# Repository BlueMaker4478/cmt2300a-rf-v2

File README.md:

# cmt2300a-rf-v2
CMT2300A RF IC Solution Ultra-low Power Sub 433-868MHz RF Transceiver

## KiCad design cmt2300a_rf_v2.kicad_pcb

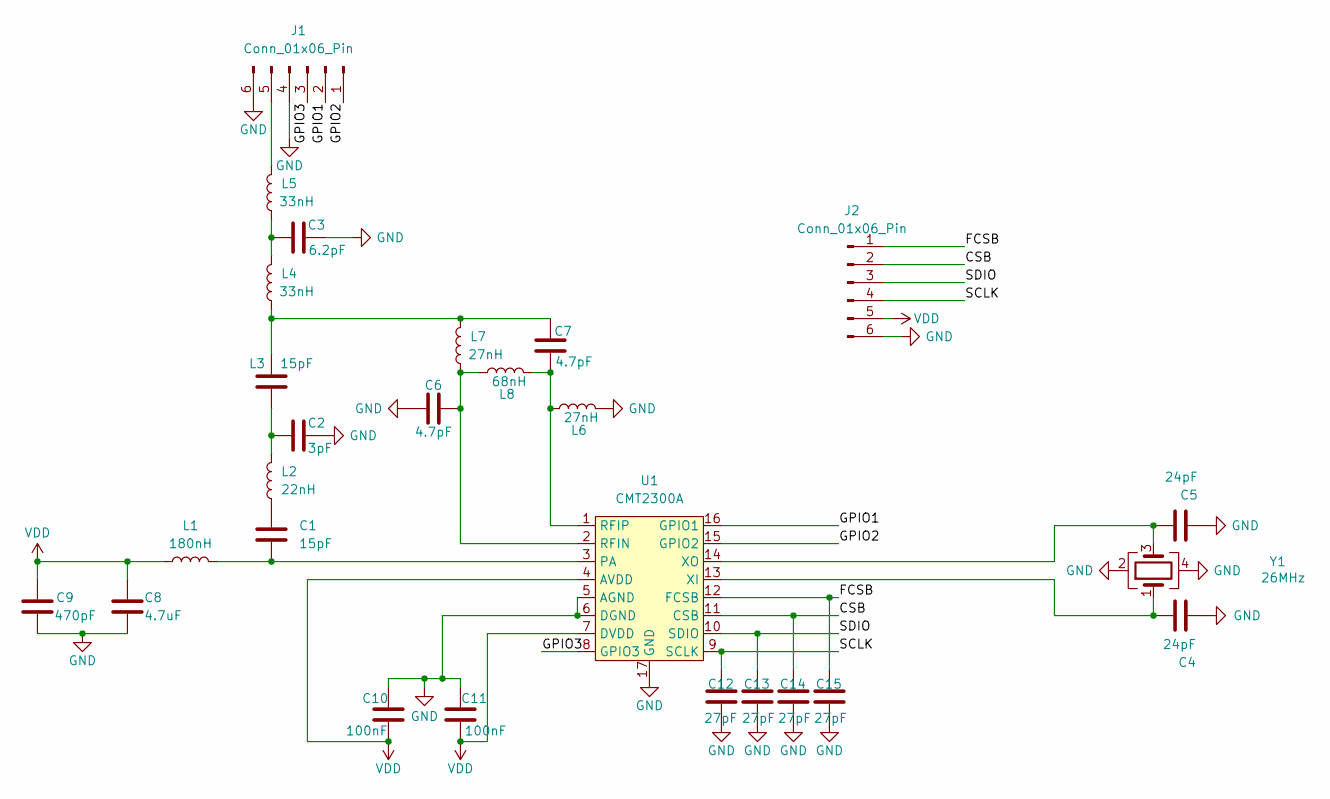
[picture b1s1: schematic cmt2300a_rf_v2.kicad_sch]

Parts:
C1: 15pF; C_0603_HandSolder
C2: 3pF; C_0603_HandSolder
C3: 6.2pF; C_0603_HandSolder
C4, C5: 24pF; C_0603_HandSolder
C6, C7: 4.7pF; C_0603_HandSolder
C8: 4.7uF; C_0603_HandSolder
C9: 470pF; C_0603_HandSolder
C10, C11: 100nF; C_0603_HandSolder
C12, C13, C14, C15: 27pF; C_0603_HandSolder
J1, J2: Conn_01x06_Pin; PinHeader_1x06_P2.54mm_Vertical
L1: 180nH; L_0603_HandSolder
L2: 22nH; L_0603_HandSolder
L3: 15pF; C_0603_HandSolder
L4, L5: 33nH; L_0603_HandSolder
L6, L7: 27nH; L_0603_HandSolder
L8: 68nH; L_0603_HandSolder
U1: CMT2300A; QFN-16-1EP_3x3mm_P0.5mm_EP1.7x1.7mm
Y1: 26MHz; Crystal_SMD_3225-4Pin_3.2x2.5mm

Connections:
/CSB: C14.1, J2.2, U1.11 (CSB)
/FCSB: C15.1, J2.1, U1.12 (FCSB)
/GPIO1: J1.2, U1.16 (GPIO1)
/GPIO2: J1.1, U1.15 (GPIO2)
/GPIO3: J1.3, U1.8 (GPIO3)
/SCLK: C12.1, J2.4, U1.9 (SCLK)
/SDIO: C13.1, J2.3, U1.10 (SDIO)
GND: C2.2, C3.2, C4.2, C5.2, C6.1, C8.2, C9.2, C10.1, C11.1, C12.2, C13.2, C14.2, C15.2, J1.4, J1.6, J2.6, L6.2, U1.5 (AGND), U1.6 (DGND), U1.17 (GND), Y1.2, Y1.4
unnamed: C1.1, L2.1
unnamed: C2.1, L2.2, L3.1
unnamed: C3.1, L4.2, L5.1
unnamed: C7.2, L3.2, L4.1, L7.2
unnamed: J1.5, L5.2
unnamed: C1.2, L1.2, U1.3 (PA)
unnamed: C6.2, L7.1, L8.1, U1.2 (RFIN)
unnamed: C7.1, L6.1, L8.2, U1.1 (RFIP)
unnamed: C4.1, U1.13 (XI), Y1.1
unnamed: C5.1, U1.14 (XO), Y1.3
VDD: C8.1, C9.1, C10.2, C11.2, J2.5, L1.1, U1.4 (AVDD), U1.7 (DVDD)

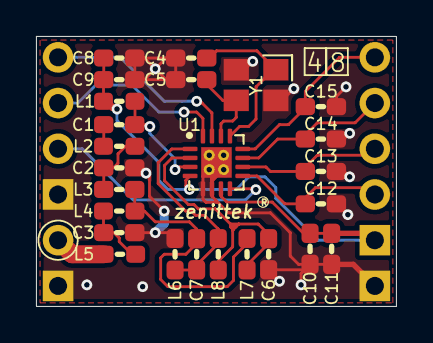
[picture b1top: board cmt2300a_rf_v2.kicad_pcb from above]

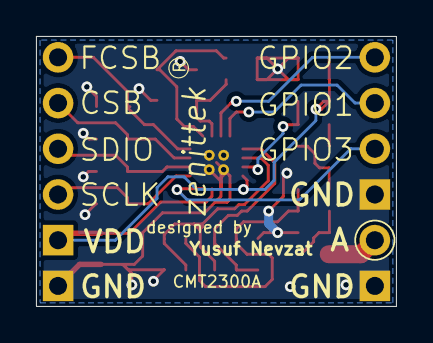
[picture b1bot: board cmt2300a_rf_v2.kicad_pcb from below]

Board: 2 copper layers, 20.0 x 15.0 mm, 27 parts (2 on the bottom side), 19 nets.

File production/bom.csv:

Designator,Footprint,Quantity,Value,LCSC Part #
"C1, L3",C_0603_HandSolder,2,15pF,
"C10, C11",C_0603_HandSolder,2,100nF,
"C12, C13, C14, C15",C_0603_HandSolder,4,27pF,
C2,C_0603_HandSolder,1,3pF,
C3,C_0603_HandSolder,1,6.2pF,
"C4, C5",C_0603_HandSolder,2,24pF,
"C6, C7",C_0603_HandSolder,2,4.7pF,
C8,C_0603_HandSolder,1,4.7uF,
C9,C_0603_HandSolder,1,470pF,
"J1, J2",PinHeader_1x06_P2.54mm_Vertical,2,Conn_01x06_Pin,
L1,L_0603_HandSolder,1,180nH,
L2,L_0603_HandSolder,1,22nH,
"L4, L5",L_0603_HandSolder,2,33nH,
"L6, L7",L_0603_HandSolder,2,27nH,
L8,L_0603_HandSolder,1,68nH,
U1,QFN-16-1EP_3x3mm_P0.5mm_EP1.7x1.7mm,1,CMT2300A,
Y1,Crystal_SMD_3225-4Pin_3.2x2.5mm,1,26MHz,

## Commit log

2025-08-08 README.md
